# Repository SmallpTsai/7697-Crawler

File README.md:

# 7697-Crawler
Tamiya 70170 crawler controlled remotely by BLE with linkit 7697 

* Please check [Youtube](https://www.youtube.com/watch?v=wKwzWoCs6b0) video!
* Please check [Slideshare](https://www.slideshare.net/SmallpTsai/7697-crawler) for more detail

## Motor driver board

This project use 2 L293D to control 3 motors. 3 motors require 6 pin to control. Used pins are listed below:

| Motor | pin A | pin B |
|-------|-------|-------|
| Left  | 17    | 16    |
| Right | 15    | 14    |
| ARM   | 13    | 12    |

* [Schematic PDF](sch/7697_motor_driver_board.pdf)
* [Eagle Schematic](sch/7697_motor_driver_board.sch)
* [Eagle Layout](sch/7697_motor_driver_board.brd)

## Arduino Source code

### Template

[Source](CrawlerControl/CrawlerControl.ino)

### Hanny's Version

##### Control UI

[Source](Crawler_Hanny/Crawler_Hanny.ino)

### Jenny's Version

##### Control UI

[Source](Crawler_Jenny/Crawler_Jenny.ino)

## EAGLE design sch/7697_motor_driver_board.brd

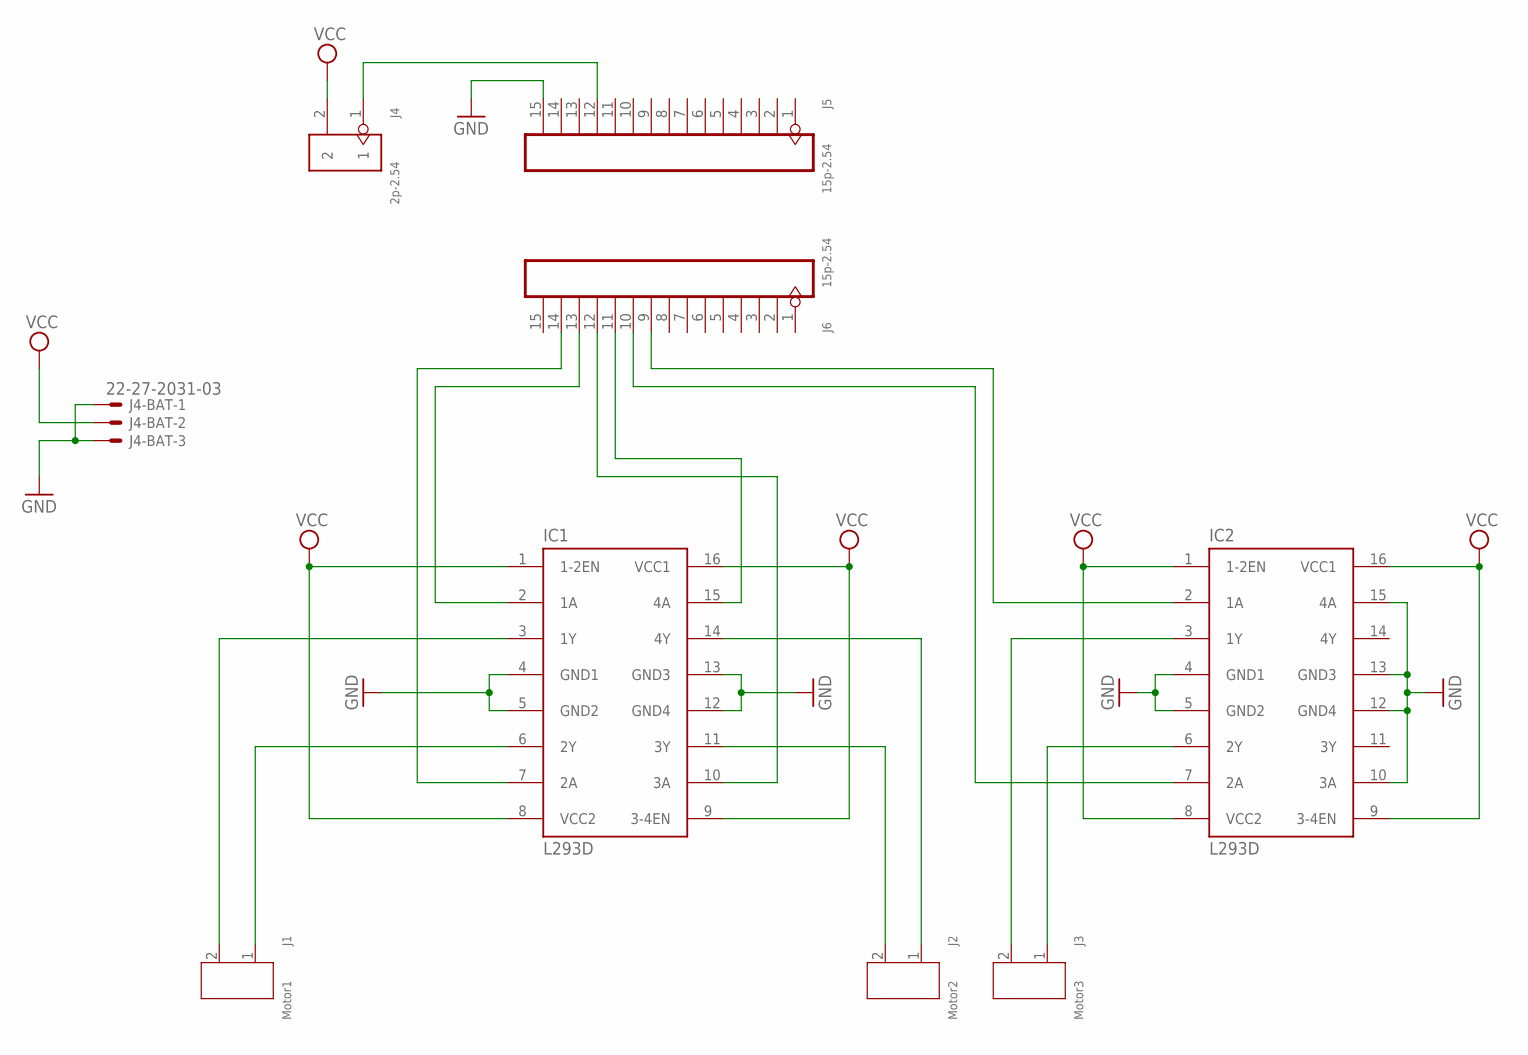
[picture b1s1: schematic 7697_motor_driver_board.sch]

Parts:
IC1, IC2: L293D; DIL16
J1: Motor1; H2-3.5-7.0X7.0MM
J2: Motor2; H2-3.5-7.0X7.0MM
J3: Motor3; H2-3.5-7.0X7.0MM
J4: 2p-2.54; H2-2.54
J4-BAT: 22-27-2031-03; 6410-03
J5, J6: 15p-2.54; H15-2.54

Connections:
GND: IC1.4 (GND1), IC1.5 (GND2), IC1.12 (GND4), IC1.13 (GND3), IC2.4 (GND1), IC2.5 (GND2), IC2.10 (3A), IC2.12 (GND4), IC2.13 (GND3), IC2.15 (4A), J4-BAT.1, J4-BAT.3, J5.15
unnamed: J4.1, J5.12
unnamed: IC1.3 (1Y), J1.2
unnamed: IC1.6 (2Y), J1.1
unnamed: IC1.11 (3Y), J2.2
unnamed: IC1.14 (4Y), J2.1
unnamed: IC2.3 (1Y), J3.2
unnamed: IC2.6 (2Y), J3.1
unnamed: IC1.7 (2A), J6.14
unnamed: IC1.2 (1A), J6.13
unnamed: IC1.10 (3A), J6.12
unnamed: IC1.15 (4A), J6.11
unnamed: IC2.7 (2A), J6.10
unnamed: IC2.2 (1A), J6.9
VCC: IC1.1 (1-2EN), IC1.8 (VCC2), IC1.9 (3-4EN), IC1.16 (VCC1), IC2.1 (1-2EN), IC2.8 (VCC2), IC2.9 (3-4EN), IC2.16 (VCC1), J4.2, J4-BAT.2

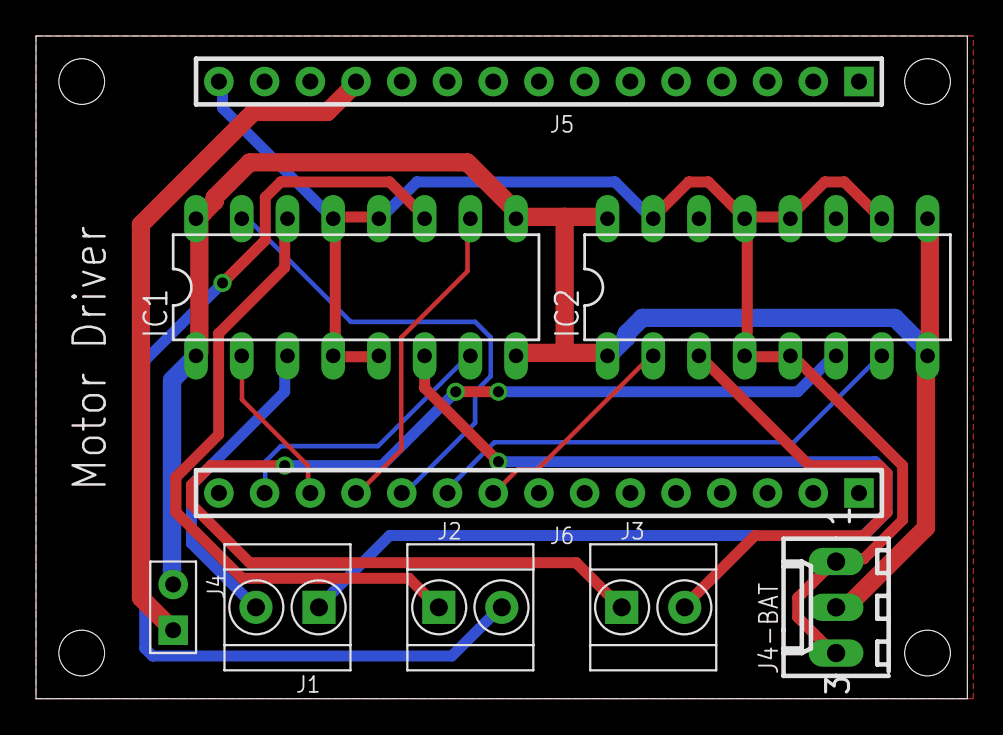
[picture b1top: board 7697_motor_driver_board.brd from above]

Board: 2 copper layers, 51.7 x 36.8 mm, 9 parts (0 on the bottom side), 15 nets.

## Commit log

2018-08-05 add source code from Hanny
2018-08-05 add images
2018-08-05 add more source
2018-08-05 add more images
